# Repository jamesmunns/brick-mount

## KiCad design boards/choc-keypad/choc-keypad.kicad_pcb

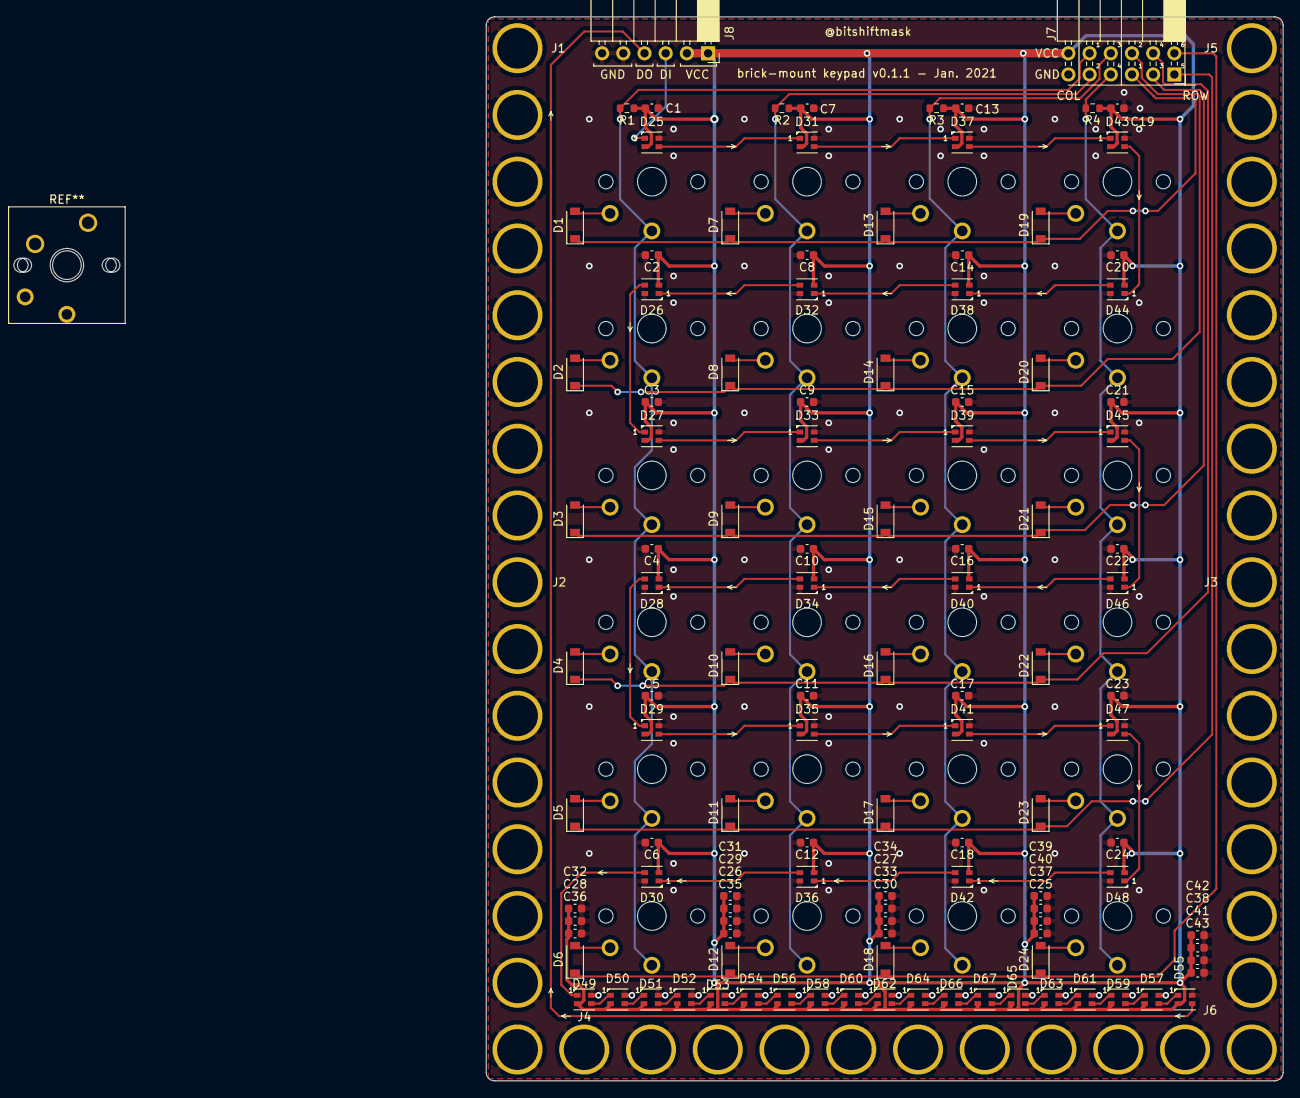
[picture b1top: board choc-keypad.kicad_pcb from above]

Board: 2 copper layers, 95.5 x 127.5 mm, 147 parts (0 on the bottom side), 80 nets.

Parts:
C1, C2, C3, C4, C5, C6, C7, C8, C9, C10, C11, C12, C13, C14, C15, C16, C17, C18, C19, C20, C21, C22, C23, C24, C25, C26, C27, C28, C29, C30, C31, C32, C33, C34, C35, C36, C37, C38, C39, C40, C41, C42, C43: 1uF; C_0603_1608Metric
D1, D2, D3, D4, D5, D6, D7, D8, D9, D10, D11, D12, D13, D14, D15, D16, D17, D18, D19, D20, D21, D22, D23, D24: D_Schottky; D_SOD-123
D25, D26, D27, D28, D29, D30, D31, D32, D33, D34, D35, D36, D37, D38, D39, D40, D41, D42, D43, D44, D45, D46, D47, D48, D49, D50, D51, D52, D53, D54, D55, D56, D57, D58, D59, D60, D61, D62, D63, D64, D65, D66, D67: TC2020-RGB; TC2020RGB
J1, J2, J3, J4, J5: Conn_01x08; brick-1x8
J6: Conn_01x02; brick-1x2
J7: Conn_02x06_Odd_Even; PinSocket_2x06_P2.54mm_Horizontal
J8: Conn_01x06; PinSocket_1x06_P2.54mm_Horizontal
R1, R2, R3, R4: 10K; R_0603_1608Metric
SW1, SW2, SW3, SW4, SW5, SW6, SW7, SW8, SW9, SW10, SW11, SW12, SW13, SW14, SW15, SW16, SW17, SW18, SW19, SW20, SW21, SW22, SW23, SW24, SW55: Choc; PG1350

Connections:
/COL1: J7.10, R1.2, SW1.1, SW2.1, SW3.1, SW4.1, SW5.1, SW6.1
/COL2: J7.9, R2.2, SW7.1, SW8.1, SW9.1, SW10.1, SW11.1, SW12.1
/COL3: J7.8, R3.2, SW13.1, SW14.1, SW15.1, SW16.1, SW17.1, SW18.1
/COL4: J7.7, R4.2, SW19.1, SW20.1, SW21.1, SW22.1, SW23.1, SW24.1
/DIN: D25.1, J8.3
/DOUT: D55.3, J8.4
/ROW1: D1.1, D7.1, D13.1, D19.1, J7.5
/ROW2: D2.1, D8.1, D14.1, D20.1, J7.6
/ROW3: D3.1, D9.1, D15.1, D21.1, J7.3
/ROW4: D4.1, D10.1, D16.1, D22.1, J7.4
/ROW5: D5.1, D11.1, D17.1, D23.1, J7.1
/ROW6: D6.1, D12.1, D18.1, D24.1, J7.2
/notification-leds/DIN: D30.3, D49.1
GND: C1.2, C2.2, C3.2, C4.2, C5.2, C6.2, C7.2, C8.2, C9.2, C10.2, C11.2, C12.2, C13.2, C14.2, C15.2, C16.2, C17.2, C18.2, C19.2, C20.2, C21.2, C22.2, C23.2, C24.2, C25.2, C26.2, C27.2, C28.2, C29.2, C30.2, C31.2, C32.2, C33.2, C34.2, C35.2, C36.2, C37.2, C38.2, C39.2, C40.2, C41.2, C42.2, C43.2, D25.4, D26.4, D27.4, D28.4, D29.4, D30.4, D31.4, D32.4, D33.4, D34.4, D35.4, D36.4, D37.4, D38.4, D39.4, D40.4, D41.4, D42.4, D43.4, D44.4, D45.4, D46.4, D47.4, D48.4, D49.4, D50.4, D51.4, D52.4, D53.4, D54.4, D55.4, D56.4, D57.4, D58.4, D59.4, D60.4, D61.4, D62.4, D63.4, D64.4, D65.4, D66.4, D67.4, J1.1, J1.2, J1.3, J1.4, J1.5, J1.6, J1.7, J1.8, J2.1, J2.2, J2.3, J2.4, J2.5, J2.6, J2.7, J2.8, J3.1, J3.2, J3.3, J3.4, J3.5, J3.6, J3.7, J3.8, J4.1, J4.2, J4.3, J4.4, J4.5, J4.6, J4.7, J4.8, J5.1, J5.2, J5.3, J5.4, J5.5, J5.6, J5.7, J5.8, J6.1, J6.2, J7.11, J8.5, J8.6
unnamed: D1.2, SW1.2
unnamed: D2.2, SW2.2
unnamed: D3.2, SW3.2
unnamed: D4.2, SW4.2
unnamed: D5.2, SW5.2
unnamed: D6.2, SW6.2
unnamed: D7.2, SW7.2
unnamed: D8.2, SW8.2
unnamed: D9.2, SW9.2
unnamed: D10.2, SW10.2
unnamed: D11.2, SW11.2
unnamed: D12.2, SW12.2
unnamed: D13.2, SW13.2
unnamed: D14.2, SW14.2
unnamed: D15.2, SW15.2
unnamed: D16.2, SW16.2
unnamed: D17.2, SW17.2
unnamed: D18.2, SW18.2
unnamed: D19.2, SW19.2
unnamed: D20.2, SW20.2
unnamed: D21.2, SW21.2
unnamed: D22.2, SW22.2
unnamed: D23.2, SW23.2
unnamed: D24.2, SW24.2
unnamed: D25.3, D31.1
unnamed: D26.1, D32.3
unnamed: D26.3, D27.1
unnamed: D27.3, D33.1
unnamed: D28.1, D34.3
unnamed: D28.3, D29.1
unnamed: D29.3, D35.1
unnamed: D30.1, D36.3
unnamed: D31.3, D37.1
unnamed: D32.1, D38.3
unnamed: D33.3, D39.1
unnamed: D34.1, D40.3
unnamed: D35.3, D41.1
unnamed: D36.1, D42.3
unnamed: D37.3, D43.1
unnamed: D38.1, D44.3
unnamed: D39.3, D45.1
unnamed: D40.1, D46.3
unnamed: D41.3, D47.1
unnamed: D42.1, D48.3
unnamed: D43.3, D44.1
unnamed: D45.3, D46.1
unnamed: D47.3, D48.1
unnamed: D49.3, D50.1
unnamed: D50.3, D51.1
unnamed: D51.3, D52.1
unnamed: D52.3, D53.1
unnamed: D53.3, D54.1
unnamed: D54.3, D56.1
unnamed: D55.1, D57.3
unnamed: D56.3, D58.1
unnamed: D57.1, D59.3
unnamed: D58.3, D60.1
unnamed: D59.1, D61.3
unnamed: D60.3, D62.1
unnamed: D61.1, D63.3
unnamed: D62.3, D64.1
unnamed: D63.1, D65.3
unnamed: D64.3, D66.1
unnamed: D65.1, D67.3
unnamed: D66.3, D67.1
VCC: C1.1, C2.1, C3.1, C4.1, C5.1, C6.1, C7.1, C8.1, C9.1, C10.1, C11.1, C12.1, C13.1, C14.1, C15.1, C16.1, C17.1, C18.1, C19.1, C20.1, C21.1, C22.1, C23.1, C24.1, C25.1, C26.1, C27.1, C28.1, C29.1, C30.1, C31.1, C32.1, C33.1, C34.1, C35.1, C36.1, C37.1, C38.1, C39.1, C40.1, C41.1, C42.1, C43.1, D25.2, D26.2, D27.2, D28.2, D29.2, D30.2, D31.2, D32.2, D33.2, D34.2, D35.2, D36.2, D37.2, D38.2, D39.2, D40.2, D41.2, D42.2, D43.2, D44.2, D45.2, D46.2, D47.2, D48.2, D49.2, D50.2, D51.2, D52.2, D53.2, D54.2, D55.2, D56.2, D57.2, D58.2, D59.2, D60.2, D61.2, D62.2, D63.2, D64.2, D65.2, D66.2, D67.2, J7.12, J8.1, J8.2, R1.1, R2.1, R3.1, R4.1

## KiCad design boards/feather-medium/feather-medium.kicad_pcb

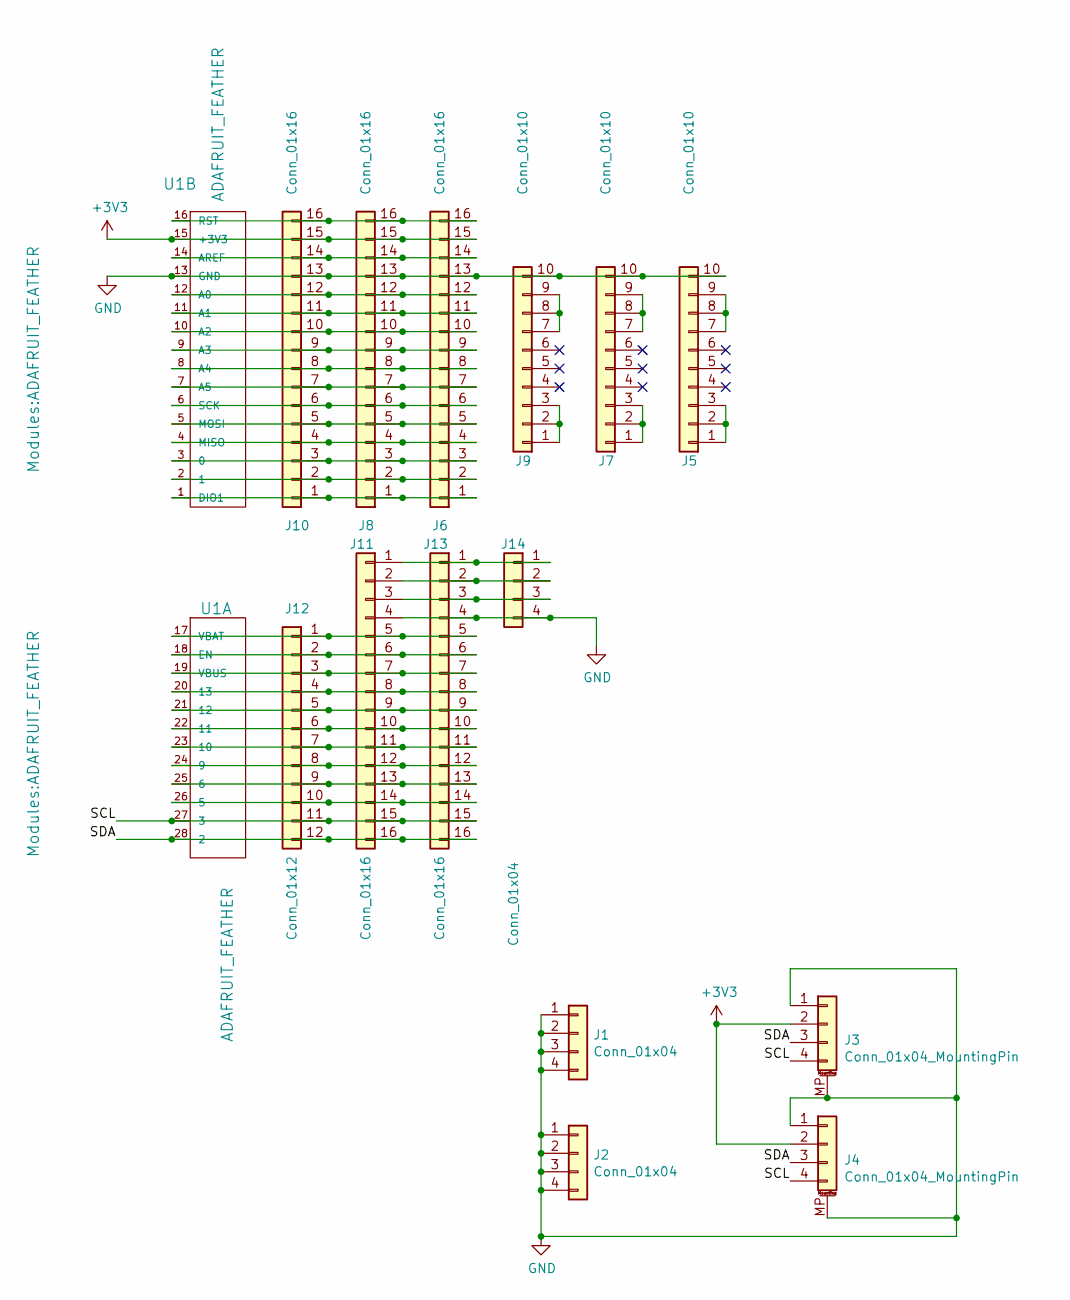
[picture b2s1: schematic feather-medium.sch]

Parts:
J1, J2: Conn_01x04; brick-1x4
J3, J4: Conn_01x04_MountingPin; JST_SH_SM04B-SRSS-TB_1x04-1MP_P1.00mm_Horizontal
J5, J7, J9: Conn_01x10; PinSocket_1x10_P2.54mm_Vertical
J6, J8, J10, J11, J13: Conn_01x16; PinSocket_1x16_P2.54mm_Vertical
J12: Conn_01x12; PinSocket_1x12_P2.54mm_Vertical
J14: Conn_01x04; PinSocket_1x04_P2.54mm_Vertical
U1: ADAFRUIT_FEATHER

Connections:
+3V3: J3.2, J4.2, J6.15, J8.15, J10.15, U1.15 (+3V3)
/SCL: J3.4, J4.4, J11.15, J12.11, J13.15, U1.27 (3)
/SDA: J3.3, J4.3, J11.16, J12.12, J13.16, U1.28 (2)
GND: J1.1, J1.2, J1.3, J1.4, J2.1, J2.2, J2.3, J2.4, J3.1, J3.MP (MountPin), J4.1, J4.MP (MountPin), J5.10, J6.13, J7.10, J8.13, J9.10, J10.13, J11.4, J13.4, J14.4, U1.13 (GND)
unnamed: J5.1, J5.2, J5.3
unnamed: J5.7, J5.8, J5.9
unnamed: J7.1, J7.2, J7.3
unnamed: J7.7, J7.8, J7.9
unnamed: J9.1, J9.2, J9.3
unnamed: J9.7, J9.8, J9.9
unnamed: J6.1, J8.1, J10.1, U1.1 (DIO1)
unnamed: J6.2, J8.2, J10.2, U1.2 (1)
unnamed: J6.3, J8.3, J10.3, U1.3 (0)
unnamed: J6.4, J8.4, J10.4, U1.4 (MISO)
unnamed: J6.5, J8.5, J10.5, U1.5 (MOSI)
unnamed: J6.6, J8.6, J10.6, U1.6 (SCK)
unnamed: J6.7, J8.7, J10.7, U1.7 (A5)
unnamed: J6.8, J8.8, J10.8, U1.8 (A4)
unnamed: J6.9, J8.9, J10.9, U1.9 (A3)
unnamed: J6.10, J8.10, J10.10, U1.10 (A2)
unnamed: J6.11, J8.11, J10.11, U1.11 (A1)
unnamed: J6.12, J8.12, J10.12, U1.12 (A0)
unnamed: J6.14, J8.14, J10.14, U1.14 (AREF)
unnamed: J6.16, J8.16, J10.16, U1.16 (RST)
unnamed: J11.1, J13.1, J14.1
unnamed: J11.2, J13.2, J14.2
unnamed: J11.3, J13.3, J14.3
unnamed: J11.5, J12.1, J13.5, U1.17 (VBAT)
unnamed: J11.6, J12.2, J13.6, U1.18 (EN)
unnamed: J11.7, J12.3, J13.7, U1.19 (VBUS)
unnamed: J11.8, J12.4, J13.8, U1.20 (13)
unnamed: J11.9, J12.5, J13.9, U1.21 (12)
unnamed: J11.10, J12.6, J13.10, U1.22 (11)
unnamed: J11.11, J12.7, J13.11, U1.23 (10)
unnamed: J11.12, J12.8, J13.12, U1.24 (9)
unnamed: J11.13, J12.9, J13.13, U1.25 (6)
unnamed: J11.14, J12.10, J13.14, U1.26 (5)

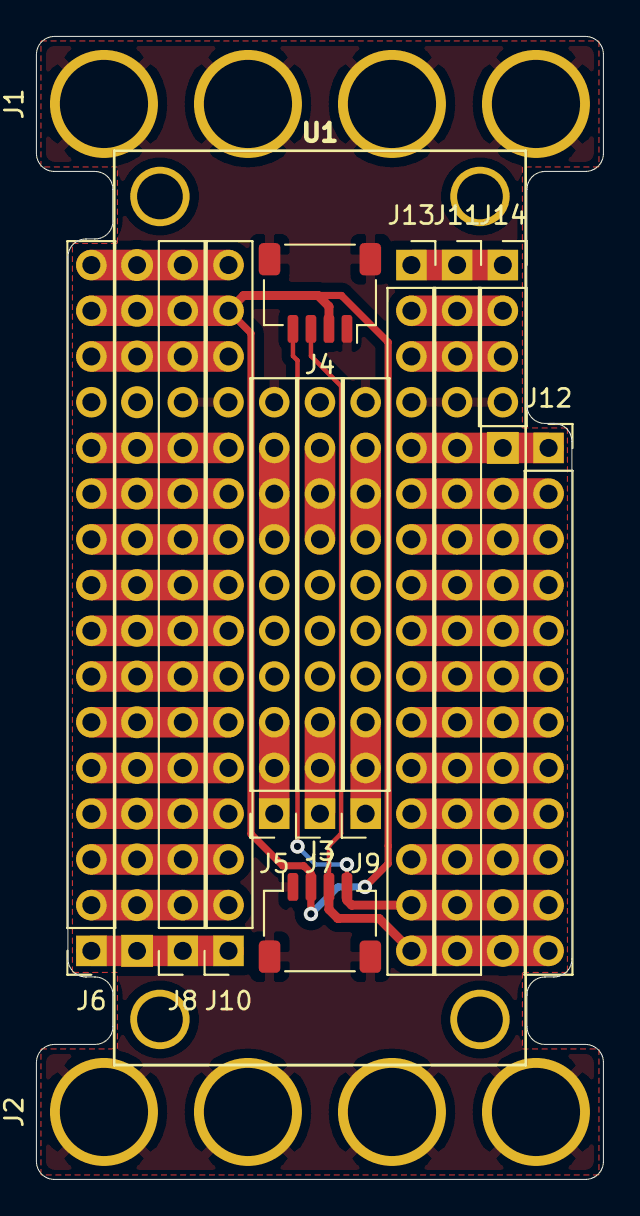
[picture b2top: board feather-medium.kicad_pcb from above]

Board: 2 copper layers, 31.5 x 63.5 mm, 15 parts (0 on the bottom side), 37 nets.

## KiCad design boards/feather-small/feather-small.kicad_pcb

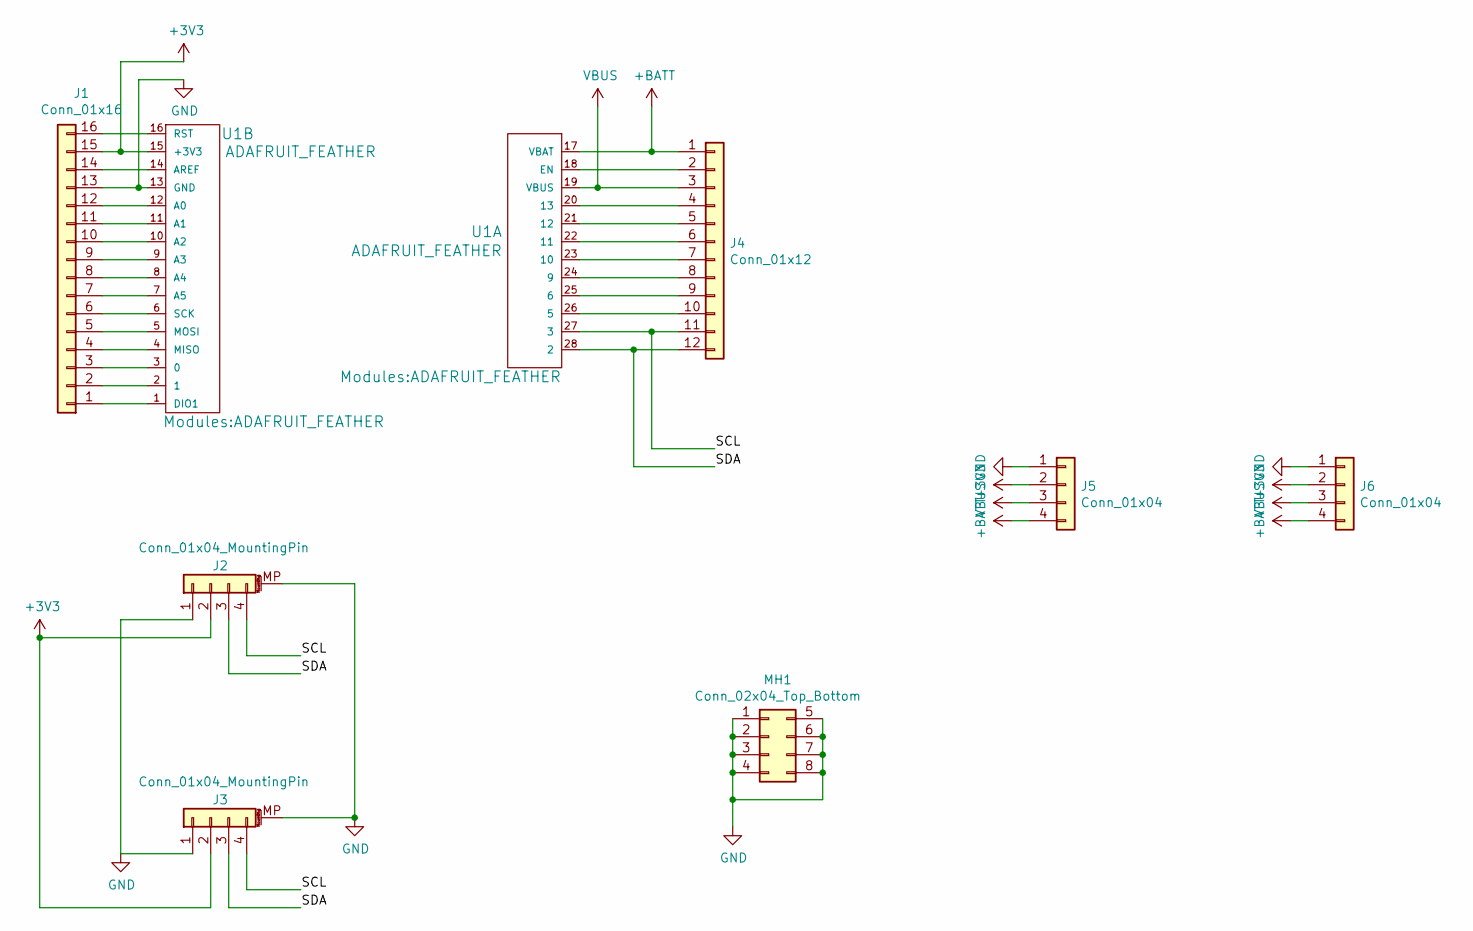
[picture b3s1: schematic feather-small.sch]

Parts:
J1: Conn_01x16; PinSocket_1x16_P2.54mm_Vertical
J2, J3: Conn_01x04_MountingPin; JST_SH_SM04B-SRSS-TB_1x04-1MP_P1.00mm_Horizontal
J4: Conn_01x12; PinSocket_1x12_P2.54mm_Vertical
J5, J6: Conn_01x04; PinSocket_1x04_P2.54mm_Vertical
MH1: Conn_02x04_Top_Bottom; brick-2x4
U1: ADAFRUIT_FEATHER

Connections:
+3V3: J1.15, J2.2, J3.2, J5.2, J6.2, U1.15 (+3V3)
+BATT: J4.1, J5.4, J6.4, U1.17 (VBAT)
/SCL: J2.4, J3.4, J4.11, U1.27 (3)
/SDA: J2.3, J3.3, J4.12, U1.28 (2)
GND: J1.13, J2.1, J2.MP (MountPin), J3.1, J3.MP (MountPin), J5.1, J6.1, MH1.1, MH1.2, MH1.3, MH1.4, MH1.5, MH1.6, MH1.7, MH1.8, U1.13 (GND)
unnamed: J1.1, U1.1 (DIO1)
unnamed: J1.2, U1.2 (1)
unnamed: J1.3, U1.3 (0)
unnamed: J1.4, U1.4 (MISO)
unnamed: J1.5, U1.5 (MOSI)
unnamed: J1.6, U1.6 (SCK)
unnamed: J1.7, U1.7 (A5)
unnamed: J1.8, U1.8 (A4)
unnamed: J1.9, U1.9 (A3)
unnamed: J1.10, U1.10 (A2)
unnamed: J1.11, U1.11 (A1)
unnamed: J1.12, U1.12 (A0)
unnamed: J1.14, U1.14 (AREF)
unnamed: J1.16, U1.16 (RST)
unnamed: J4.2, U1.18 (EN)
unnamed: J4.4, U1.20 (13)
unnamed: J4.5, U1.21 (12)
unnamed: J4.6, U1.22 (11)
unnamed: J4.7, U1.23 (10)
unnamed: J4.8, U1.24 (9)
unnamed: J4.9, U1.25 (6)
unnamed: J4.10, U1.26 (5)
VBUS: J4.3, J5.3, J6.3, U1.19 (VBUS)

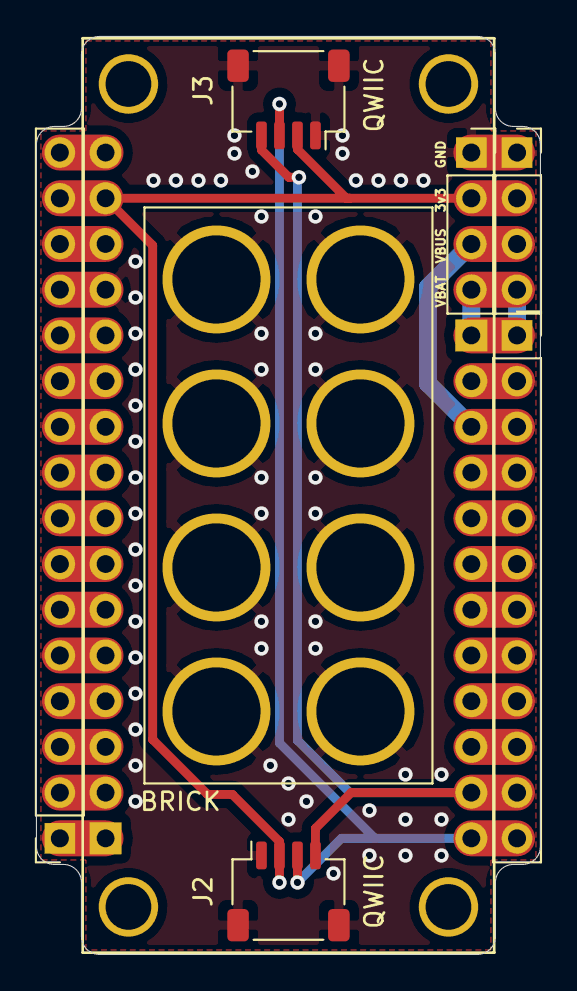
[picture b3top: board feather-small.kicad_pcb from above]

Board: 2 copper layers, 28.0 x 51.0 mm, 8 parts (0 on the bottom side), 28 nets.
